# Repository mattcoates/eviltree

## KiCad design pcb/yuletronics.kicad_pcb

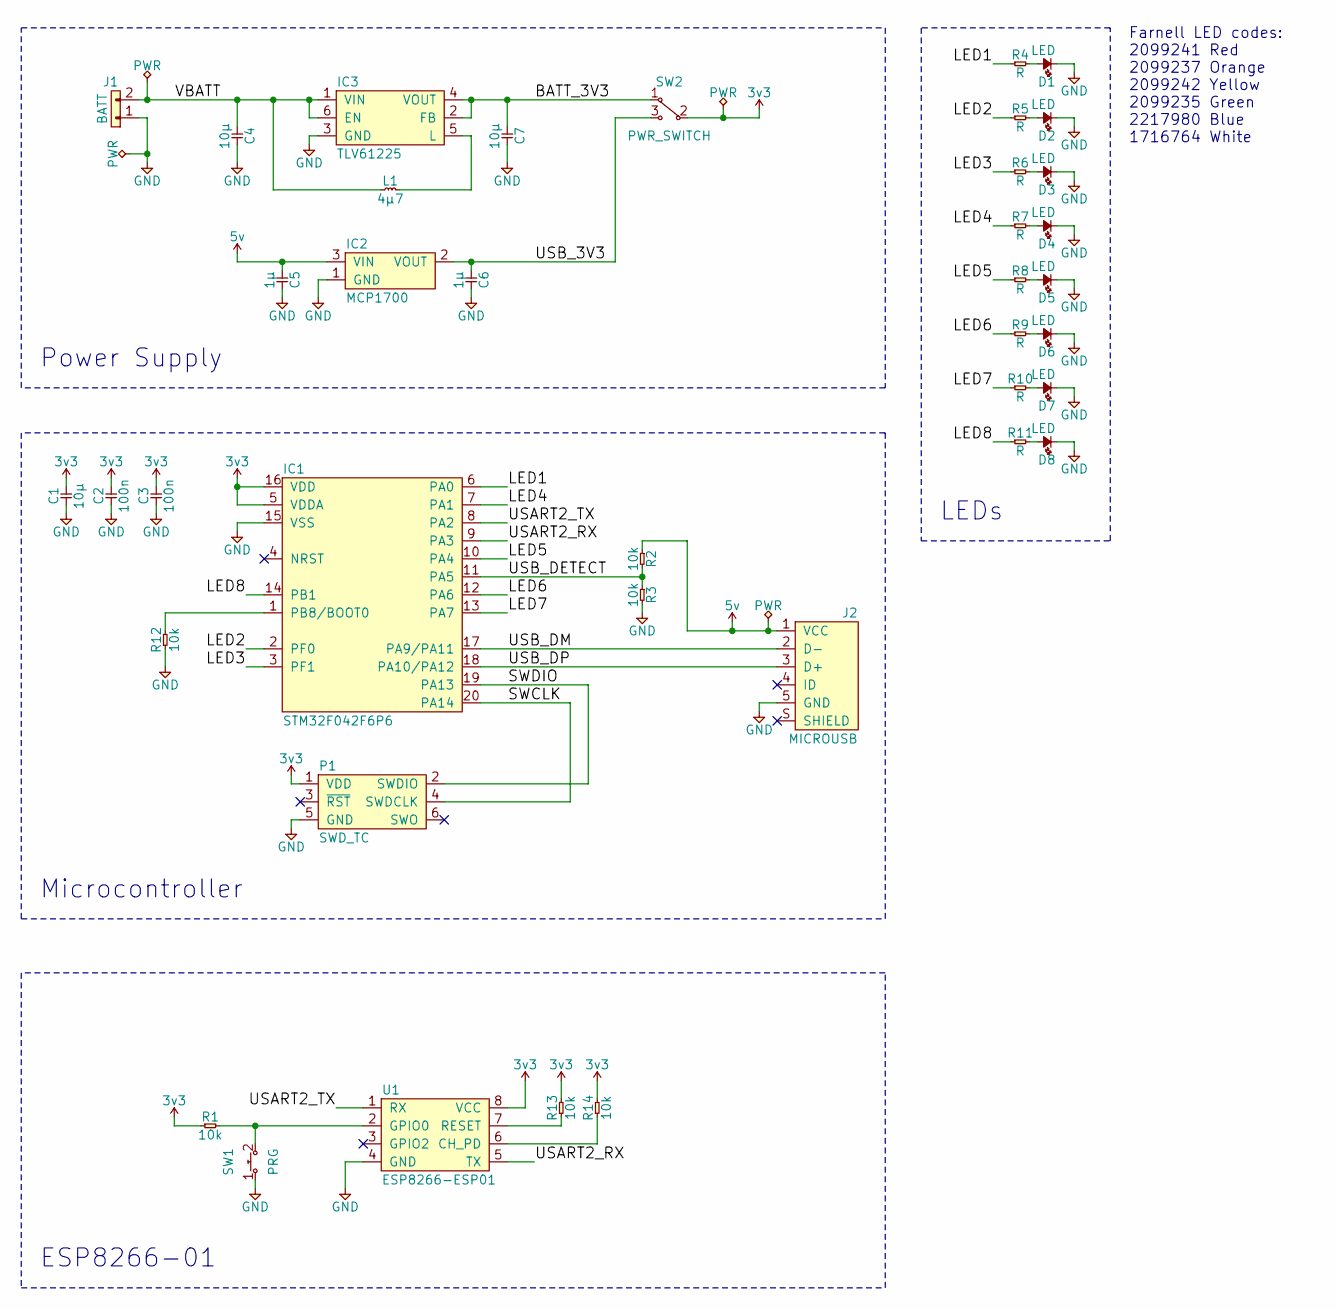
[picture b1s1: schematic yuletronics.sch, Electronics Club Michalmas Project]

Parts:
C1, C4, C7: 10µ; 0805; Farnell 2320851
C2, C3: 100n; 0805; Farnell 1759265
C5, C6: 1µ; 0805; Farnell 2320853
D1, D3, D5, D7: LED; 0805-LED; Farnell 2099241
D2, D4, D6, D8: LED; 0805-LED; Farnell 2099235
IC1: STM32F042F6P6; TSSOP-20; Farnell 2469549
IC2: MCP1700; SOT-23; Farnell 1296592
IC3: TLV61225; SC-70-6; Farnell 2492362
J1: BATT; AAA_HOLDER; Farnell 1702632
J2: MICROUSB; MICROUSB_MOLEX_47589-0001; Farnell 1568023
L1: 4µ7; 2016M; Farnell 2616849
P1: SWD_TC; TC2030-NL
R1, R2, R3, R12, R13, R14: 10k; 0805; Farnell 9332391
R4, R5, R6, R7, R8, R9, R10, R11: R; 0805
SW1: PRG; MOM_SWITCH; Farnell 2056809
SW2: PWR_SWITCH; SPDT_SWITCH; Farnell 1201430
U1: ESP8266-ESP01

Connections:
3v3: C1.2, C2.2, C3.2, IC1.5 (VDDA), IC1.16 (VDD), P1.1 (VDD), R1.1, R13.2, R14.2, SW2.2, U1.8 (VCC)
5v: C5.1, IC2.3 (VIN), J2.1 (VCC), R2.1
/BATT_3V3: C7.1, IC3.2 (FB), IC3.4 (VOUT), SW2.1
/LED1: IC1.6 (PA0), R4.1
/LED2: IC1.2 (PF0), R5.1
/LED3: IC1.3 (PF1), R6.1
/LED4: IC1.7 (PA1), R7.1
/LED5: IC1.10 (PA4), R8.1
/LED6: IC1.12 (PA6), R9.1
/LED7: IC1.13 (PA7), R10.1
/LED8: IC1.14 (PB1), R11.1
/SWCLK: IC1.20 (PA14), P1.4 (SWDCLK)
/SWDIO: IC1.19 (PA13), P1.2 (SWDIO)
/USART2_RX: IC1.9 (PA3), U1.5 (TX)
/USART2_TX: IC1.8 (PA2), U1.1 (RX)
/USB_3V3: C6.1, IC2.2 (VOUT), SW2.3
/USB_DETECT: IC1.11 (PA5), R2.2, R3.1
/USB_DM: IC1.17 (PA9/PA11), J2.2 (D-)
/USB_DP: IC1.18 (PA10/PA12), J2.3 (D+)
/VBATT: C4.1, IC3.1 (VIN), IC3.6 (EN), J1.2, L1.1
GND: C1.1, C2.1, C3.1, C4.2, C5.2, C6.2, C7.2, D1.1, D2.1, D3.1, D4.1, D5.1, D6.1, D7.1, D8.1, IC1.15 (VSS), IC2.1 (GND), IC3.3 (GND), J1.1, J2.5 (GND), P1.5 (GND), R3.2, R12.1, SW1.1, U1.4 (GND)
unnamed: D1.2, R4.2
unnamed: D2.2, R5.2
unnamed: D3.2, R6.2
unnamed: D4.2, R7.2
unnamed: D5.2, R8.2
unnamed: D6.2, R9.2
unnamed: D7.2, R10.2
unnamed: D8.2, R11.2
unnamed: IC1.1 (PB8/BOOT0), R12.2
unnamed: IC3.5 (L), L1.2
unnamed: R1.2, SW1.2, U1.2 (GPIO0)
unnamed: R13.1, U1.7 (RESET)
unnamed: R14.1, U1.6 (CH_PD)

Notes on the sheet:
Power Supply
Microcontroller
LEDs
Farnell LED codes: 2099241 Red 2099237 Orange 2099242 Yellow 2099235 Green 2217980 Blue 1716764 White
ESP8266-01

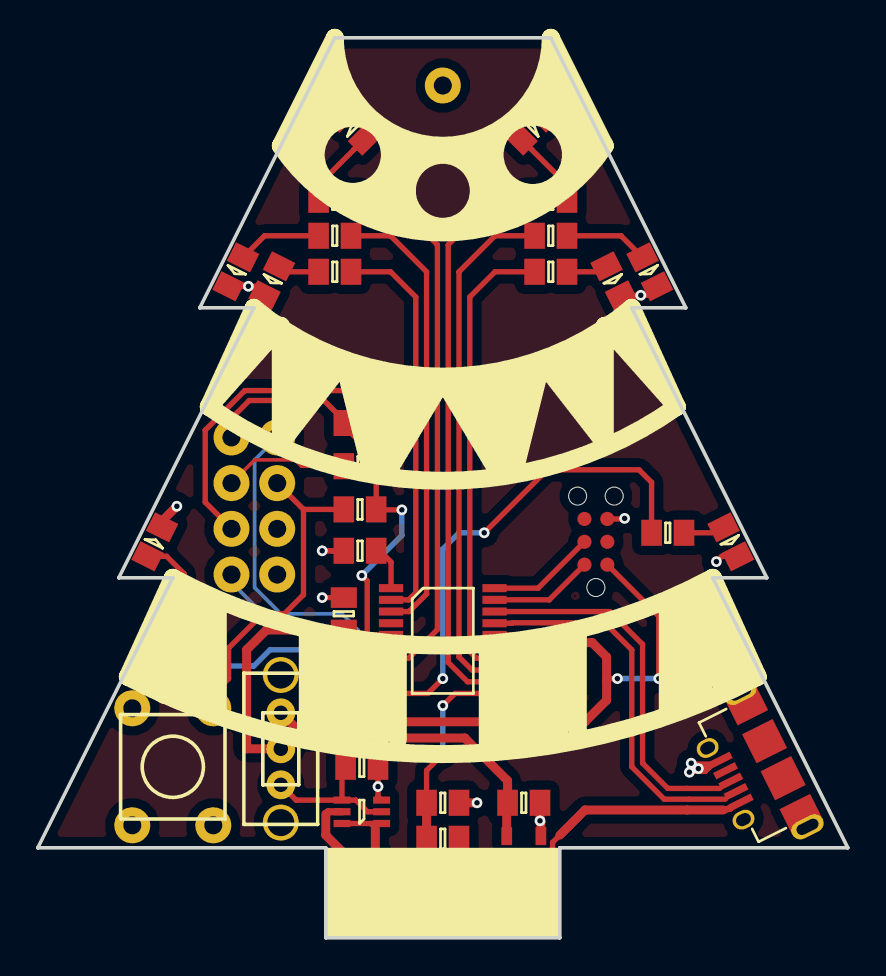
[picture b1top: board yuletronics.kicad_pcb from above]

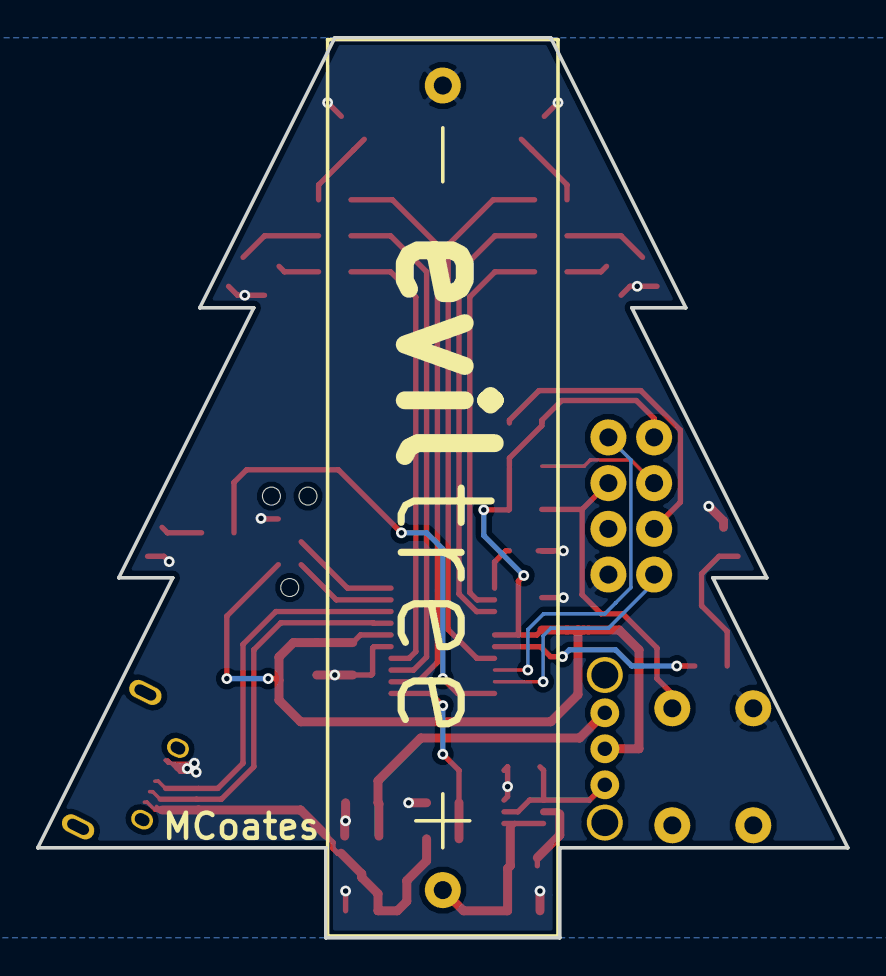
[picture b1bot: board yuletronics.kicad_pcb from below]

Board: 2 copper layers, 45.0 x 50.0 mm, 39 parts (2 on the bottom side), 34 nets.

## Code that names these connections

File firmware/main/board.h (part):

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/*
 *  GPIOA setup:
 *
 * PA0  - LED1                         (af2).
 * PA1  - LED4                         (af2).
 * PA2  - PIN2                         (unused).
 * PA3  - PIN3                         (unused).
 * PA4  - LED5                         (output, pushpull, startlow).
 * PA5  - PIN5                         (unused).
 * PA6  - LED6                         (af1).
 * PA7  - LED7                         (af1).
 * PA8  - PIN8                         (unused).
 * PA9  - PIN9                         (unused).
 * PA10 - PIN10                        (unused).
 * PA11 - USB_DM                       (input).
 * PA12 - USB_DP                       (input).
 * PA13 - SWDIO                        (af0).
 * PA14 - SWCLK                        (pulldown, af0).
 * PA15 - PIN15                        (unused).
*/
#define VAL_GPIOA_MODER                (PIN_MODE_ALTERNATE(GPIOA_LED1) | \
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 *  GPIOB setup:
 *
 * PB0  - PIN0                         (unused).
 * PB1  - LED8                         (af1).
 * PB2  - PIN2                         (unused).
 * PB3  - PIN3                         (unused).
 * PB4  - PIN4                         (unused).
 * PB5  - PIN5                         (unused).
 * PB6  - PIN6                         (unused).
 * PB7  - PIN7                         (unused).
 * PB8  - PIN8                         (unused).
 * PB9  - PIN9                         (unused).
 * PB10 - PIN10                        (unused).
 * PB11 - PIN11                        (unused).
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/*
 *  GPIOF setup:
 *
 * PF0  - LED2                         (output, pushpull, startlow).
 * PF1  - LED3                         (output, pushpull, startlow).
 * PF2  - PIN2                         (unused).
 * PF3  - PIN3                         (unused).
 * PF4  - PIN4                         (unused).
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
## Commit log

2016-10-26 Initial Download
2016-10-26 Added ESP
2016-10-26 Export Gerbers
2016-11-02 Final Changes
2016-12-02 Firmware things

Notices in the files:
firmware/main/board.h:
ChibiOS - Copyright (C) 2006..2016 Giovanni Di Sirio
Licensed under the Apache License, Version 2.0 (the "License");
